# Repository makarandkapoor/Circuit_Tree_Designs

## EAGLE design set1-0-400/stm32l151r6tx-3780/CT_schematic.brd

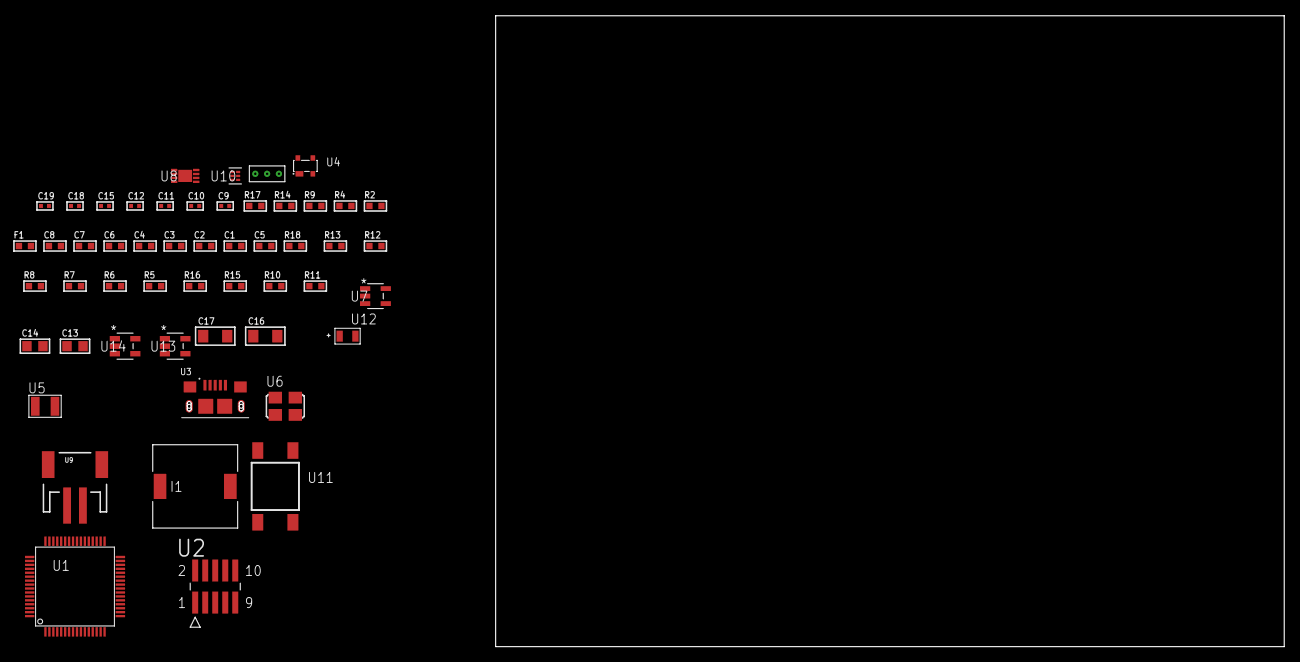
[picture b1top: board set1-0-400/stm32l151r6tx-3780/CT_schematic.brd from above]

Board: 2 copper layers, 52 parts (0 on the bottom side), 30 nets, no tracks yet.

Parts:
C1, C2, C3, C4, C6: 1e-07; C0603
C5: 4.7e-06; C0603
C7: 1e-08; C0603
C8: 1e-06; C0603
C9, C10: 1e-11; C0402
C11, C15: 1e-07; C0402
C12, C18, C19: 1e-08; C0402
C13, C14: 1e-05; C0805
C16, C17: 1e-05; C1206
F1: 240.0; L0603
I1: 3.8e-06; DR1040
R2: 1000.0; R0603
R4: 4700.0; R0603
R5, R6, R7, R8, R12, R13, R18: 10000.0; R0603
R9: 5.0; R0603
R10: 220000.0; R0603
R11: 1000000.0; R0603
R14: 9100.0; R0603
R15: 680000.0; R0603
R16: 120000.0; R0603
R17: 2000.0; R0603
U1: STM32L151R6T6; LQFP64
U2: FTSH-105-01-L-DV-K; SAMTEC_FTSH-105-01-L-DV-K
U3: 10118193-0001LF; FCI_10118193-0001LF
U4: prtr5v0u2ax; SOT143B
U5: ABS07-32.768KHZ-7-T
U6: ASFL1-25MHZ-NCS; ASFL1
U7: ltc3406es5; TSOT-23-5
U8: MCP73831T-2ACI/MC; DFN8_2X3MC
U9: S2B-PH-SM4-TB(LF)(SN); JST-2-SMD
U10: TPS3895ADRYR; SON-6
U11: 4-1437565-2; SW_4-1437565-2
U12: Q65110A2395; LGM67K-G1J2-24-Z
U13, U14: nc7sz125m5x; NC7SZ125M5X
U15: Dummy; DUMMY_PACKAGE_112

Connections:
CLK_CRYSTAL_U1_3: C9.1, U1.3, U5.1
CLK_CRYSTAL_U1_4: C10.1, U1.4, U5.2
CLK_U1_5: U1.5, U6.3
GND: C1.2, C2.2, C3.2, C4.2, C5.2, C6.2, C7.2, C8.2, C9.2, C10.2, C11.2, C12.2, C13.2, C14.1, C14.2, C15.2, C16.2, C17.2, C18.2, C19.2, R2.2, R5.2, R9.2, R10.2, R14.2, R16.2, R17.2, U1.12, U1.18, U1.31, U1.47, U1.63, U2.3, U2.5, U3.5, U3.6, U3.7, U3.8, U3.9, U4.1, U6.2, U7.2, U8.6, U8.9, U9.2, U10.2, U12.C, U13.2, U13.3, U14.1, U14.3, U15.1
INPUT_USBPOWER_5V: C16.1, R18.2, U3.1, U4.4, U8.1, U8.2
NET_U1_1: C6.1, U1.1
NET_U1_7: R4.1, U1.7, U14.4
NET_U1_13: C7.1, C8.1, F1.1, U1.13
NET_U1_60: R5.1, U1.60
NET_U1_62: U11.3, U11.4
NET_U2_9: R9.1, U2.9
NET_U7_3: I1.1, U7.3
NET_U7_5: R10.1, R11.1, U7.5
NET_U7_ATNET_3: I1.2, R11.2
NET_U8_5: R18.1, U8.5
NET_U8_8: R17.1, U8.8
NET_U10_1: R13.1, R14.1, U10.1
NET_U10_3: R15.2, R16.1, U10.3
NET_U10_4: R12.1, U10.4, U13.4, U14.2
NET_U11_1: R2.1, U11.1, U11.2
PROC_SYS_JTCK_SWCLK: R7.1, U1.49, U2.4
PROC_SYS_JTDO_TRACESWO: U1.55, U2.6
PROC_SYS_JTMS_SWDIO: R8.1, U1.46, U2.2
PROC_TIM10_CH1: U1.22, U15.2
PROC_TIM11_CH1: U1.23, U15.3
PROC_USB_DM: U1.44, U3.2, U4.3
PROC_USB_DP: U1.45, U3.3, U4.2
RST_OUT_U2_JTAG_RST_B: R6.1, U2.10, U13.1
VCC_S1_3V7: C13.1, C17.1, U7.4, U8.3, U8.4, U9.1
VCC_TIER1_3V3: C1.1, C2.1, C3.1, C4.1, C5.1, C11.1, C12.1, C14.2, C15.1, C18.1, C19.1, F1.2, I1.2, R4.2, R6.2, R7.2, R8.2, R11.2, R12.2, R13.2, R15.1, U1.19, U1.32, U1.48, U1.64, U2.1, U6.4, U10.6, U13.5, U14.5

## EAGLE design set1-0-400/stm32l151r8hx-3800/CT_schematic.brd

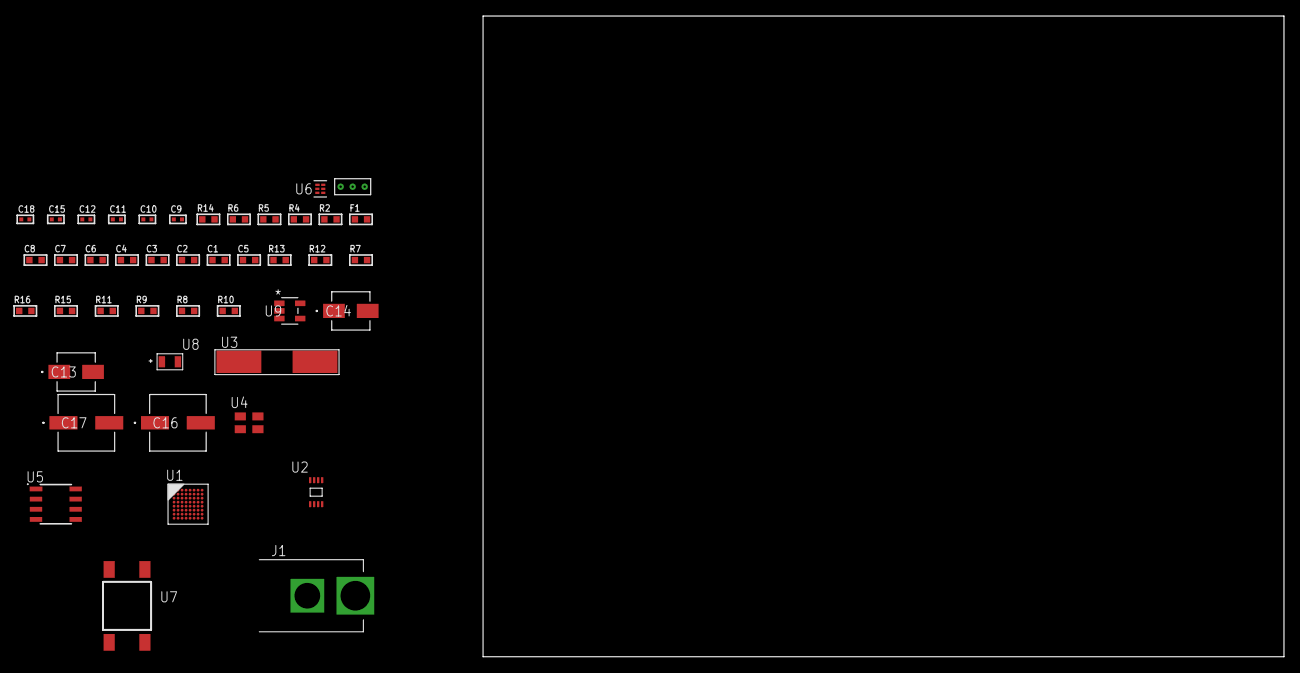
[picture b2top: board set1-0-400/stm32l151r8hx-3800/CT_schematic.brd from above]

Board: 2 copper layers, 100.0 x 80.0 mm, 44 parts (0 on the bottom side), 22 nets, no tracks yet.

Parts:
C1, C2, C3, C4, C6: 1e-07; C0603
C5: 4.7e-06; C0603
C7: 1e-08; C0603
C8: 1e-06; C0603
C9, C10: 1e-11; C0402
C11, C12, C18: 1e-08; C0402
C13: 1e-06; EXV-9B
C14: 2.2e-06; EXV-9B
C15: 1e-07; C0402
C16, C17: 0.0001; EXV-9H
F1: 240.0; L0603
J1: PJ-037B; PJ-037B_PACKAGE
R2: 1000.0; R0603
R4: 4700.0; R0603
R5, R6: 2200.0; R0603
R7, R12, R13: 10000.0; R0603
R8, R9, R11: 100000.0; R0603
R10: 164658.62; R0603
R14: 9100.0; R0603
R15: 680000.0; R0603
R16: 120000.0; R0603
U1: STM32L151R8H6; TFBGA64
U2: 24AA16-I/MC; TDFN-8/6MM
U3: ABLS-25.000MHZ-B2F-T
U4: ASEK-32.768KHz-ECST; ASEK
U5: LP2954AIMX/NOPB; LP2954
U6: TPS3895ADRYR; SON-6
U7: 4-1437565-2; SW_4-1437565-2
U8: Q65110A2395; LGM67K-G1J2-24-Z
U9: nc7sz125m5x; NC7SZ125M5X
U10: Dummy; DUMMY_PACKAGE_90

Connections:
CLK_CRYSTAL_U1_C1: C9.1, U1.C1, U3.1
CLK_CRYSTAL_U1_D1: C10.1, U1.D1, U3.2
CLK_U1_A1: U1.A1, U4.3
GND: C1.2, C2.2, C3.2, C4.2, C5.2, C6.2, C7.2, C8.2, C9.2, C10.2, C11.2, C12.2, C13.2, C14.2, C15.2, C16.2, C17.2, C18.2, J1.2, R2.2, R7.2, R11.2, R14.2, R16.2, U1.C2, U1.D4, U1.D5, U1.D6, U1.F1, U2.4, U2.7, U4.2, U5.4, U6.2, U8.C, U9.1, U9.3, U10.1
NET_U1_A3: R6.1, U1.A3, U2.5
NET_U1_B2: C6.1, U1.B2
NET_U1_B3: R5.1, U1.B3, U2.6
NET_U1_B4: R7.1, U1.B4
NET_U1_E1: R4.1, U1.E1, U9.4
NET_U1_H1: C7.1, C8.1, F1.1, U1.G1, U1.H1
NET_U1_H8: U7.3, U7.4
NET_U5_3: R9.1, U5.3
NET_U5_5: R8.1, U5.5
NET_U5_7: R10.2, R11.1, U5.7
NET_U6_1: R13.1, R14.1, U6.1
NET_U6_3: R15.2, R16.1, U6.3
NET_U6_4: R12.1, U6.4, U9.2
NET_U7_1: R2.1, U7.1, U7.2
PROC_TIM2_CH1: U1.A6, U10.3
PROC_TIM2_CH3: U1.F3, U10.2
VCC_S1_5V6: C13.1, C16.1, C17.1, J1.1, R9.2, U5.8
VCC_TIER1_3V3: C1.1, C2.1, C3.1, C4.1, C5.1, C11.1, C12.1, C14.1, C15.1, C18.1, F1.2, R4.2, R5.2, R6.2, R8.2, R10.1, R12.2, R13.2, R15.1, U1.D2, U1.E4, U1.E5, U1.E6, U2.8, U4.4, U5.1, U6.6, U9.5

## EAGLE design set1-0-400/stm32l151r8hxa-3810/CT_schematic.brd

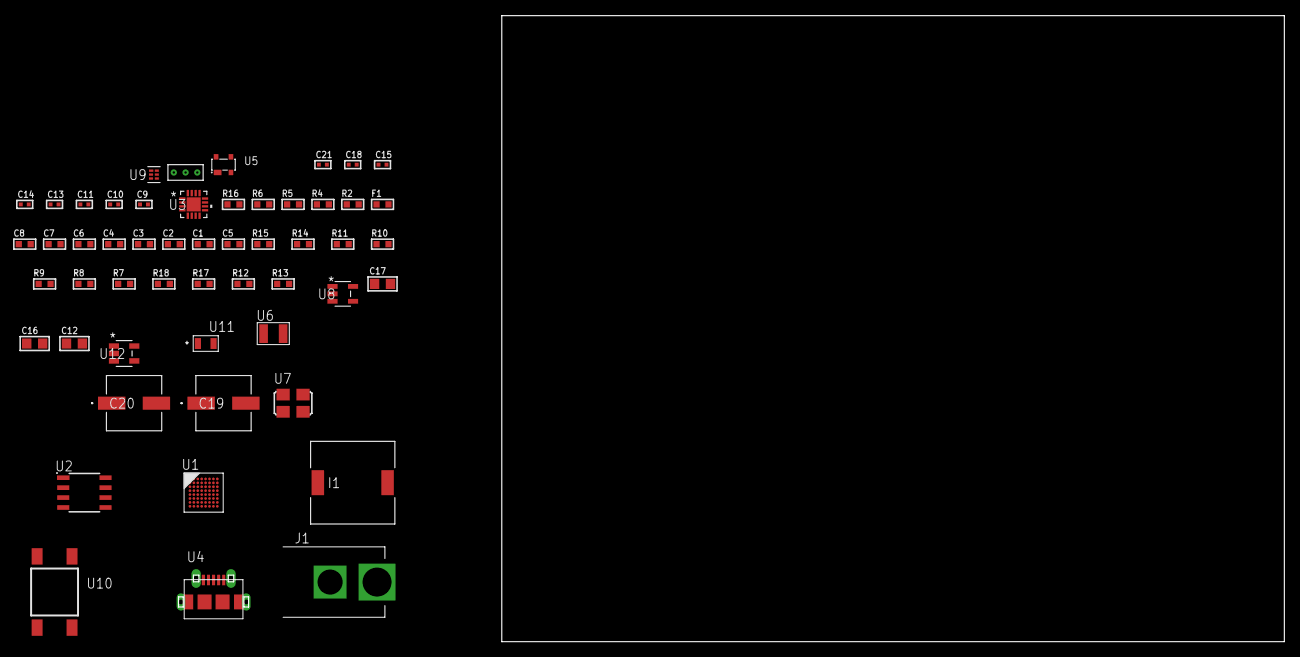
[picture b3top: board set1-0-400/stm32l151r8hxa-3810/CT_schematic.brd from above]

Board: 2 copper layers, 53 parts (0 on the bottom side), 33 nets, no tracks yet.

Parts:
C1, C2, C3, C4, C6: 1e-07; C0603
C5: 4.7e-06; C0603
C7: 1e-08; C0603
C8: 1e-06; C0603
C9, C10: 1e-11; C0402
C11, C15, C21: 1e-08; C0402
C12: 4.7e-06; C0805
C13, C14, C18: 1e-07; C0402
C16, C17: 1e-05; C0805
C19, C20: 0.0001; EXV-9H
F1: 240.0; L0603
I1: 8.2e-06; DR1040
J1: PJ-037B; PJ-037B_PACKAGE
R2: 1000.0; R0603
R4: 4700.0; R0603
R5, R6: 2200.0; R0603
R7, R8, R9, R10, R11, R14, R15: 10000.0; R0603
R12: 220000.0; R0603
R13: 1000000.0; R0603
R16: 9100.0; R0603
R17: 680000.0; R0603
R18: 120000.0; R0603
U1: STM32L151R8H6A; TFBGA64
U2: AT25M02-SSHD-T; SOIC-8
U3: MMA8451QT; QFN-16
U4: 47590-0001; MICRO_USB_AB
U5: prtr5v0u2ax; SOT143B
U6: ABS07-32.768KHZ-7-T
U7: ASFL1-25MHZ-NCS; ASFL1
U8: ltc3406es5; TSOT-23-5
U9: TPS3895ADRYR; SON-6
U10: 4-1437565-2; SW_4-1437565-2
U11: Q65110A2395; LGM67K-G1J2-24-Z
U12: nc7sz125m5x; NC7SZ125M5X
U13: Dummy; DUMMY_PACKAGE_111

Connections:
CLK_CRYSTAL_U1_A1: C9.1, U1.A1, U6.1
CLK_CRYSTAL_U1_B1: C10.1, U1.B1, U6.2
CLK_U1_C1: U1.C1, U7.3
GND: C1.2, C2.2, C3.2, C4.2, C5.2, C6.2, C7.2, C8.2, C9.2, C10.2, C11.2, C12.2, C13.2, C14.2, C15.2, C16.2, C17.1, C17.2, C18.2, C19.2, C20.2, C21.2, J1.2, R2.2, R7.2, R11.2, R12.2, R16.2, R18.2, U1.C2, U1.D4, U1.D5, U1.D6, U1.F1, U2.4, U3.5, U3.10, U3.12, U3.17, U4.5, U4.6, U4.7, U4.8, U4.9, U5.1, U7.2, U8.2, U9.2, U11.C, U12.1, U12.3, U13.1
NET_U1_A3: R6.1, U1.A3, U3.6
NET_U1_B2: C6.1, U1.B2
NET_U1_B3: R5.1, U1.B3, U3.4
NET_U1_B4: R7.1, U1.B4
NET_U1_E1: R4.1, U1.E1, U12.4
NET_U1_H1: C7.1, C8.1, F1.1, U1.G1, U1.H1
NET_U1_H8: U10.3, U10.4
NET_U2_3: R8.1, U2.3
NET_U2_7: R10.1, U2.7
NET_U3_2: C14.1, U3.2
NET_U3_7: R11.1, U3.7
NET_U5_4: U4.1, U5.4
NET_U8_3: I1.1, U8.3
NET_U8_5: R12.1, R13.1, U8.5
NET_U8_ATNET_3: I1.2, R13.2
NET_U9_1: R15.1, R16.1, U9.1
NET_U9_3: R17.2, R18.1, U9.3
NET_U9_4: R14.1, U9.4, U12.2
NET_U10_1: R2.1, U10.1, U10.2
PROC_SPI1_MISO: U1.A4, U2.2
PROC_SPI1_MOSI: U1.C4, U2.5
PROC_SPI1_NSS: R9.1, U1.A6, U2.1
PROC_SPI1_SCK: U1.A5, U2.6
PROC_TIM2_CH3: U1.F3, U13.2
PROC_TIM2_CH4: U1.G3, U13.3
PROC_USB_DM: U1.C8, U4.2, U5.3
PROC_USB_DP: U1.B8, U4.3, U5.2
VCC_S1_4V8: C16.1, C19.1, C20.1, J1.1, U8.4
VCC_TIER1_3V3: C1.1, C2.1, C3.1, C4.1, C5.1, C11.1, C12.1, C13.1, C15.1, C17.2, C18.1, C21.1, F1.2, I1.2, R4.2, R5.2, R6.2, R8.2, R9.2, R10.2, R13.2, R14.2, R15.2, R17.1, U1.D2, U1.E4, U1.E5, U1.E6, U2.8, U3.1, U3.14, U7.4, U9.6, U12.5

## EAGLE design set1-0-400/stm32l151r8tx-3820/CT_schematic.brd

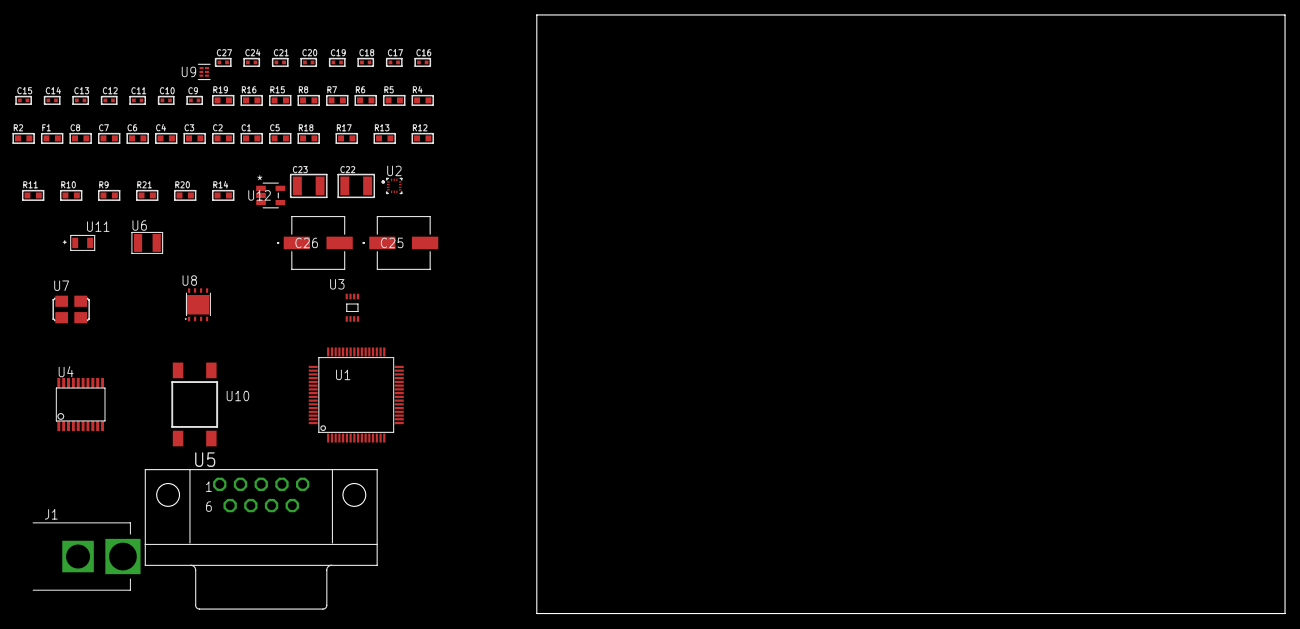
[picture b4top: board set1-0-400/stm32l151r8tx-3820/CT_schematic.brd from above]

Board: 2 copper layers, 100.0 x 80.0 mm, 60 parts (0 on the bottom side), 39 nets, no tracks yet.

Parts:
C1, C2, C3, C4, C6: 1e-07; C0603
C5: 4.7e-06; C0603
C7: 1e-08; C0603
C8: 1e-06; C0603
C9, C10: 1e-11; C0402
C11, C12, C14, C15, C16, C17, C18, C19, C24: 1e-07; C0402
C13, C20, C21, C27: 1e-08; C0402
C22, C23: 1e-05; C1210
C25, C26: 0.0001; EXV-9H
F1: 240.0; L0603
J1: PJ-037B; PJ-037B_PACKAGE
R2, R16: 1000.0; R0603
R4: 4700.0; R0603
R5, R6, R7, R8: 2200.0; R0603
R9, R10, R11, R12, R13, R17, R18: 10000.0; R0603
R14: 100000.0; R0603
R15: 2231.0; R0603
R19: 9100.0; R0603
R20: 680000.0; R0603
R21: 120000.0; R0603
U1: STM32L151R8T6; LQFP64
U2: BMC150; LGA14R35P5X6_200X200X100
U3: 24AA32AT-I/MNY; TDFN-8/6MM
U4: SP3203ECY-L/TR; TSSOP20-I
U5: 182-009-113R531; 182-009-MALE
U6: ABS07-32.768KHZ-7-T
U7: ASFL1-25MHZ-NCS; ASFL1
U8: LP3878SDX-ADJ/NOPB; WSON-8
U9: TPS3895ADRYR; SON-6
U10: 4-1437565-2; SW_4-1437565-2
U11: Q65110A2395; LGM67K-G1J2-24-Z
U12: nc7sz125m5x; NC7SZ125M5X

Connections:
CLK_CRYSTAL_U1_3: C9.1, U1.3, U6.1
CLK_CRYSTAL_U1_4: C10.1, U1.4, U6.2
CLK_U1_5: U1.5, U7.3
GND: C1.2, C2.2, C3.2, C4.2, C5.2, C6.2, C7.2, C8.2, C9.2, C10.2, C11.2, C12.2, C13.2, C14.2, C15.2, C18.2, C19.2, C20.2, C21.2, C22.2, C23.2, C24.2, C25.2, C26.2, C27.2, J1.2, R2.2, R9.2, R11.2, R12.2, R16.2, R19.2, R21.2, U1.12, U1.18, U1.31, U1.47, U1.63, U2.1, U2.6, U2.7, U2.9, U3.4, U4.18, U5.5, U7.2, U8.3, U8.PAD, U9.2, U11.C, U12.1, U12.3
NET_U1_1: C6.1, U1.1
NET_U1_7: R4.1, U1.7, U12.4
NET_U1_13: C7.1, C8.1, F1.1, U1.13
NET_U1_29: R7.1, U1.29, U3.6
NET_U1_30: R8.1, U1.30, U3.5
NET_U1_58: R5.1, U1.58, U2.11
NET_U1_59: R6.1, U1.59, U2.14
NET_U1_60: R9.1, U1.60
NET_U1_62: U10.3, U10.4
NET_U3_1: R11.1, U3.1
NET_U3_2: R12.1, U3.2
NET_U3_3: R13.1, U3.3
NET_U4_1: C16.1, U4.1
NET_U4_2: C18.1, U4.2
NET_U4_3: C16.2, U4.3
NET_U4_4: C17.1, U4.4
NET_U4_5: C17.2, U4.5
NET_U4_6: C19.1, U4.6
NET_U5_2: U4.14, U5.2
NET_U5_3: U4.17, U5.3
NET_U5_7: U4.13, U5.7
NET_U5_8: U4.16, U5.8
NET_U8_1: C21.1, U8.1
NET_U8_6: R15.2, R16.1, U8.6
NET_U8_8: R14.1, U8.8
NET_U9_1: R18.1, R19.1, U9.1
NET_U9_3: R20.2, R21.1, U9.3
NET_U9_4: R17.1, U9.4, U12.2
NET_U10_1: R2.1, U10.1, U10.2
PROC_USART1_CTS: U1.44, U4.8
PROC_USART1_RTS: U1.45, U4.10
PROC_USART1_RX: U1.43, U4.11
PROC_USART1_TX: U1.42, U4.7
VCC_S1_12V7: C22.1, C25.1, C26.1, J1.1, R14.2, U8.4
VCC_TIER1_3V3: C1.1, C2.1, C3.1, C4.1, C5.1, C11.1, C12.1, C13.1, C14.1, C15.1, C20.1, C23.1, C24.1, C27.1, F1.2, R4.2, R5.2, R6.2, R7.2, R8.2, R10.1, R10.2, R13.2, R15.1, R17.2, R18.2, R20.1, U1.19, U1.32, U1.48, U1.64, U2.8, U2.10, U2.12, U2.13, U3.7, U3.8, U4.12, U4.19, U7.4, U8.5, U9.6, U12.5

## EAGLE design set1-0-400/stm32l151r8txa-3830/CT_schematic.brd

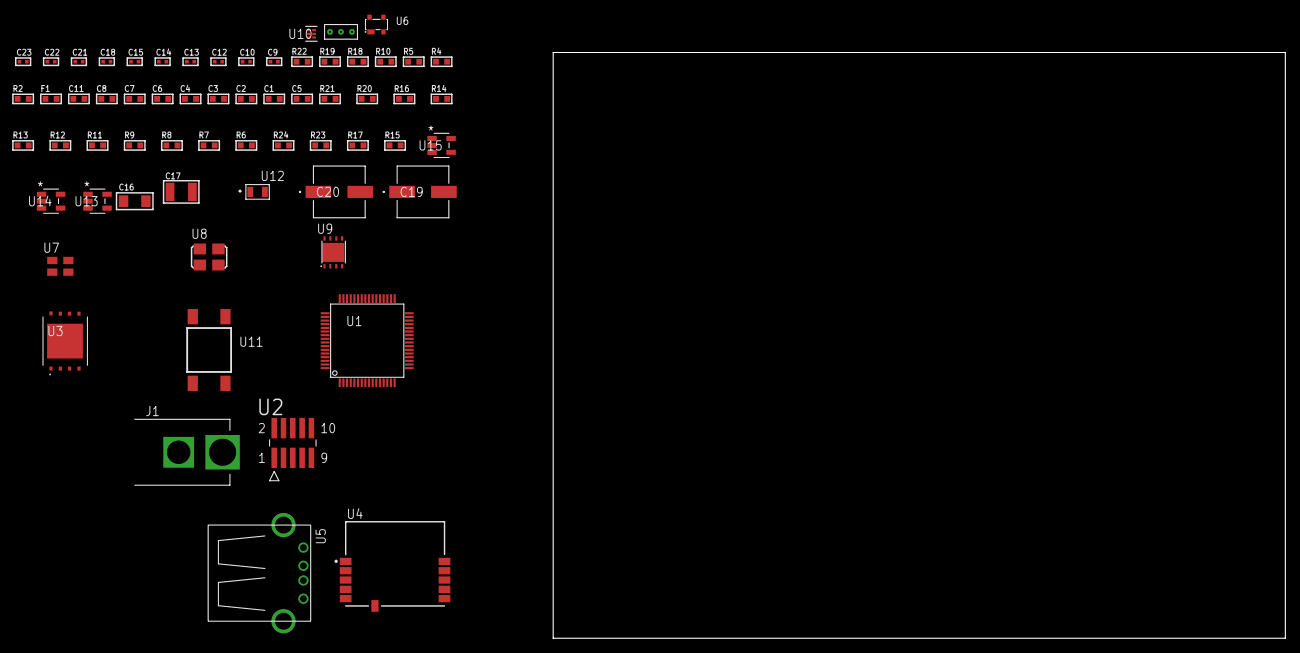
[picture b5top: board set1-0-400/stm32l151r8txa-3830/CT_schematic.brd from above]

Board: 2 copper layers, 100.0 x 80.0 mm, 63 parts (0 on the bottom side), 39 nets, no tracks yet.

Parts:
C1, C2, C3, C4, C6: 1e-07; C0603
C5: 4.7e-06; C0603
C7: 1e-08; C0603
C8, C11: 1e-06; C0603
C9, C12, C18: 1e-07; C0402
C10, C13, C14, C15, C21, C22, C23: 1e-08; C0402
C16: 1e-05; C1206
C17: 1e-05; C1210
C19, C20: 0.0001; EXV-9H
F1: 240.0; L0603
J1: PJ-037B; PJ-037B_PACKAGE
R2, R19: 1000.0; R0603
R4, R5: 4700.0; R0603
R6, R7, R8, R9, R11, R12, R13, R14, R20, R21: 10000.0; R0603
R10: 5.0; R0603
R15, R17: 100000.0; R0603
R16: 47000.0; R0603
R18: 2231.0; R0603
R22: 9100.0; R0603
R23: 680000.0; R0603
R24: 120000.0; R0603
U1: STM32L151R8T6A; LQFP64
U2: FTSH-105-01-L-DV-K; SAMTEC_FTSH-105-01-L-DV-K
U3: S25FL128SDPNFI001; WNG008
U4: SPBTLE-RF; XCVR_SPBTLE-RF
U5: 61400416021; USB-A-H
U6: prtr5v0u2ax; SOT143B
U7: ASEK-32.768KHz-ECST; ASEK
U8: ASFL1-25MHZ-NCS; ASFL1
U9: LP3878SDX-ADJ/NOPB; WSON-8
U10: TPS3895ADRYR; SON-6
U11: 4-1437565-2; SW_4-1437565-2
U12: Q65110A2395; LGM67K-G1J2-24-Z
U13, U14, U15: nc7sz125m5x; NC7SZ125M5X
U16: Dummy; DUMMY_PACKAGE_140

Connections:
CLK_U1_3: U1.3, U7.3
CLK_U1_5: U1.5, U8.3
GND: C1.2, C2.2, C3.2, C4.2, C5.2, C6.2, C7.2, C8.2, C9.2, C10.2, C11.2, C12.2, C13.2, C14.2, C15.2, C16.2, C17.2, C18.2, C19.2, C20.2, C21.2, C22.2, C23.2, J1.2, R2.2, R6.2, R10.2, R15.2, R16.2, R19.2, R22.2, R24.2, U1.12, U1.18, U1.31, U1.47, U1.63, U2.3, U2.5, U3.4, U3.PAD, U4.6, U5.4, U5.5, U5.6, U6.1, U7.2, U8.2, U9.3, U9.PAD, U10.2, U12.C, U13.2, U13.3, U14.1, U14.3, U15.1, U15.3, U16.1
NET_U1_1: C6.1, U1.1
NET_U1_7: R5.1, U1.7, U15.4
NET_U1_13: C7.1, C8.1, F1.1, U1.13
NET_U1_60: R6.1, U1.60
NET_U1_62: U11.3, U11.4
NET_U2_9: R10.1, U2.9
NET_U3_3: R11.1, U3.3
NET_U3_7: R13.1, U3.7
NET_U4_11: R4.1, U4.11, U14.4
NET_U6_4: U5.1, U6.4
NET_U9_1: C15.1, U9.1
NET_U9_6: R18.2, R19.1, U9.6
NET_U9_8: R17.1, U9.8
NET_U10_1: R21.1, R22.1, U10.1
NET_U10_3: R23.2, R24.1, U10.3
NET_U10_4: R20.1, U10.4, U13.4, U14.2, U15.2
NET_U11_1: R2.1, U11.1, U11.2
PROC_GPIO_TO_U4_SPI_IRQ: R16.1, U1.2, U4.4
PROC_PC15_OSC32_OUT: U1.4, U16.2
PROC_PH1_OSC_OUT: U1.6, U16.3
PROC_SPI1_MISO: U1.22, U4.8
PROC_SPI1_MOSI: U1.23, U4.9
PROC_SPI1_NSS: R14.1, U1.20, U4.10
PROC_SPI1_SCK: R15.1, U1.21, U4.7
PROC_SPI2_MISO: U1.35, U3.2
PROC_SPI2_MOSI: U1.36, U3.5
PROC_SPI2_NSS: R12.1, U1.33, U3.1
PROC_SPI2_SCK: U1.34, U3.6
PROC_SYS_JTCK_SWCLK: R8.1, U1.49, U2.4
PROC_SYS_JTDO_TRACESWO: U1.55, U2.6
PROC_SYS_JTMS_SWDIO: R9.1, U1.46, U2.2
PROC_USB_DM: U1.44, U5.2, U6.3
PROC_USB_DP: U1.45, U5.3, U6.2
RST_OUT_U2_JTAG_RST_B: R7.1, U2.10, U13.1
VCC_S1_9V4: C16.1, C19.1, C20.1, J1.1, R17.2, U9.4
VCC_TIER1_3V3: C1.1, C2.1, C3.1, C4.1, C5.1, C9.1, C10.1, C11.1, C12.1, C13.1, C14.1, C17.1, C18.1, C21.1, C22.1, C23.1, F1.2, R4.2, R5.2, R7.2, R8.2, R9.2, R11.2, R12.2, R13.2, R14.2, R18.1, R20.2, R21.2, R23.1, U1.19, U1.32, U1.48, U1.64, U2.1, U3.8, U4.5, U7.4, U8.4, U9.5, U10.6, U13.5, U14.5, U15.5

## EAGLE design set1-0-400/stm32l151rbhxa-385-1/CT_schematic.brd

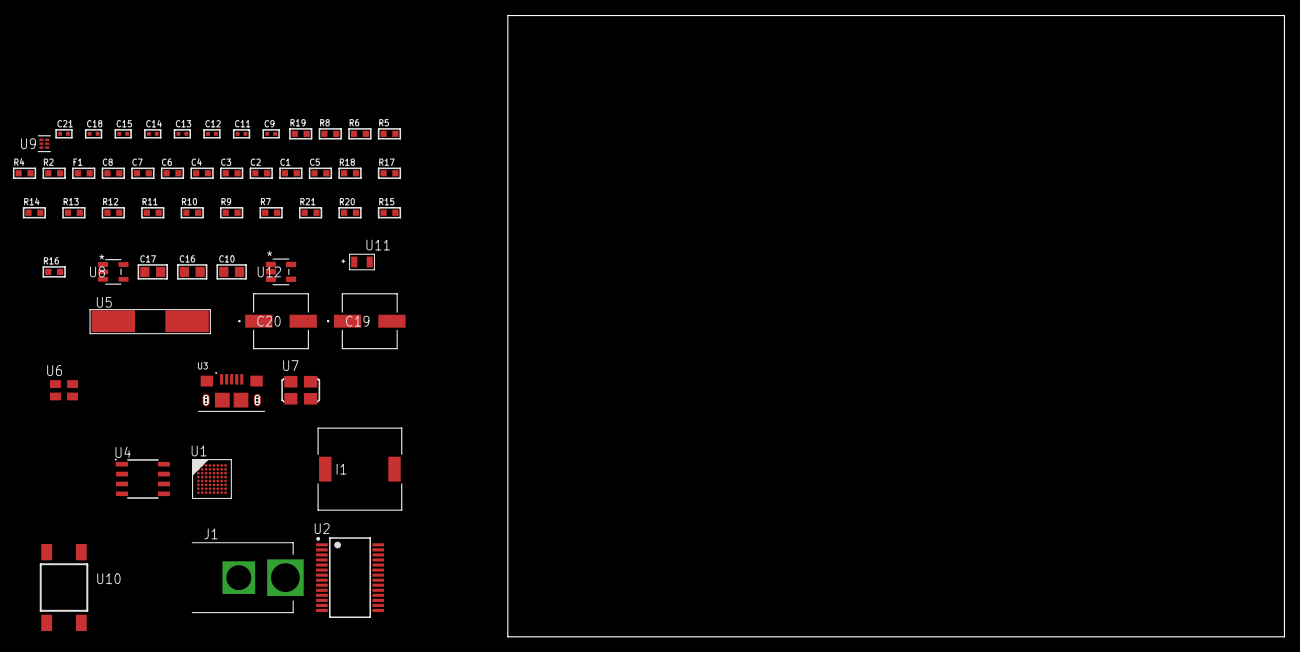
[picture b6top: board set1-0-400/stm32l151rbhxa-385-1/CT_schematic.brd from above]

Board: 2 copper layers, 55 parts (0 on the bottom side), 35 nets, no tracks yet.

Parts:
C1, C2, C3, C4, C6: 1e-07; C0603
C5: 4.7e-06; C0603
C7: 1e-08; C0603
C8: 1e-06; C0603
C9, C11, C12, C13, C18: 1e-07; C0402
C10: 4.7e-06; C0805
C14, C15, C21: 1e-08; C0402
C16, C17: 1e-05; C0805
C19, C20: 0.0001; EXV-9H
F1: 240.0; L0603
I1: 5.2e-06; DR1040
J1: PJ-037B; PJ-037B_PACKAGE
R2: 1000.0; R0603
R4, R8: 4700.0; R0603
R5, R6: 2200.0; R0603
R7, R9, R10, R11, R12, R13, R14, R17, R18: 10000.0; R0603
R15: 220000.0; R0603
R16: 1000000.0; R0603
R19: 9100.0; R0603
R20: 680000.0; R0603
R21: 120000.0; R0603
U1: STM32L151RBH6A; TFBGA64
U2: FT232RL-REEL; SSOP-28
U3: 10118193-0001LF; FCI_10118193-0001LF
U4: TMP75BID; SOIC-8
U5: ABLS-12.000MHZ-B4-T
U6: ASEK-32.768KHz-ECST; ASEK
U7: ASFL1-25MHZ-NCS; ASFL1
U8: ltc3406es5; TSOT-23-5
U9: TPS3895ADRYR; SON-6
U10: 4-1437565-2; SW_4-1437565-2
U11: Q65110A2395; LGM67K-G1J2-24-Z
U12: nc7sz125m5x; NC7SZ125M5X

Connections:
CLK_CRYSTAL_U2_27: U2.27, U5.1
CLK_CRYSTAL_U2_28: U2.28, U5.2
CLK_U1_A1: U1.A1, U6.3
CLK_U1_C1: U1.C1, U7.3
GND: C1.2, C2.2, C3.2, C4.2, C5.2, C6.2, C7.2, C8.2, C9.2, C10.2, C11.2, C12.2, C13.2, C14.2, C15.2, C16.2, C17.1, C17.2, C18.2, C19.2, C20.2, C21.2, J1.2, R2.2, R7.2, R10.2, R13.2, R15.2, R19.2, R21.2, U1.C2, U1.D4, U1.D5, U1.D6, U1.F1, U2.7, U2.18, U2.21, U2.25, U2.26, U3.5, U3.6, U3.7, U3.8, U3.9, U4.4, U6.2, U7.2, U8.2, U9.2, U11.C, U12.1, U12.3
NET_U1_A3: R6.1, U1.A3, U4.1
NET_U1_B2: C6.1, U1.B2
NET_U1_B3: R5.1, U1.B3, U4.2
NET_U1_B4: R7.1, U1.B4
NET_U1_E1: R4.1, U1.E1, U12.4
NET_U1_H1: C7.1, C8.1, F1.1, U1.G1, U1.H1
NET_U1_H8: U10.3, U10.4
NET_U2_14: R9.1, U2.14
NET_U2_17: C11.1, U2.17
NET_U2_19: R10.1, U2.19
NET_U3_1: R8.1, U3.1
NET_U3_2: U2.16, U3.2
NET_U3_3: U2.15, U3.3
NET_U4_3: R11.1, U4.3
NET_U4_5: R14.1, U4.5
NET_U4_6: R13.1, U4.6
NET_U4_7: R12.1, U4.7
NET_U8_3: I1.1, U8.3
NET_U8_5: R15.1, R16.1, U8.5
NET_U8_ATNET_3: I1.2, R16.2
NET_U9_1: R18.1, R19.1, U9.1
NET_U9_3: R20.2, R21.1, U9.3
NET_U9_4: R17.1, U9.4, U12.2
NET_U10_1: R2.1, U10.1, U10.2
PROC_USART1_CTS: U1.C8, U2.3
PROC_USART1_RTS: U1.B8, U2.11
PROC_USART1_RX: U1.C3, U2.1
PROC_USART1_TX: U1.C7, U2.5
VCC_S1_5V2: C16.1, C19.1, C20.1, J1.1, U8.4
VCC_TIER1_3V3: C1.1, C2.1, C3.1, C4.1, C5.1, C9.1, C10.1, C12.1, C13.1, C14.1, C15.1, C17.2, C18.1, C21.1, F1.2, I1.2, R4.2, R5.2, R6.2, R9.2, R11.2, R12.2, R14.2, R16.2, R17.2, R18.2, R20.1, U1.D2, U1.E4, U1.E5, U1.E6, U2.4, U2.20, U4.8, U6.4, U7.4, U9.6, U12.5

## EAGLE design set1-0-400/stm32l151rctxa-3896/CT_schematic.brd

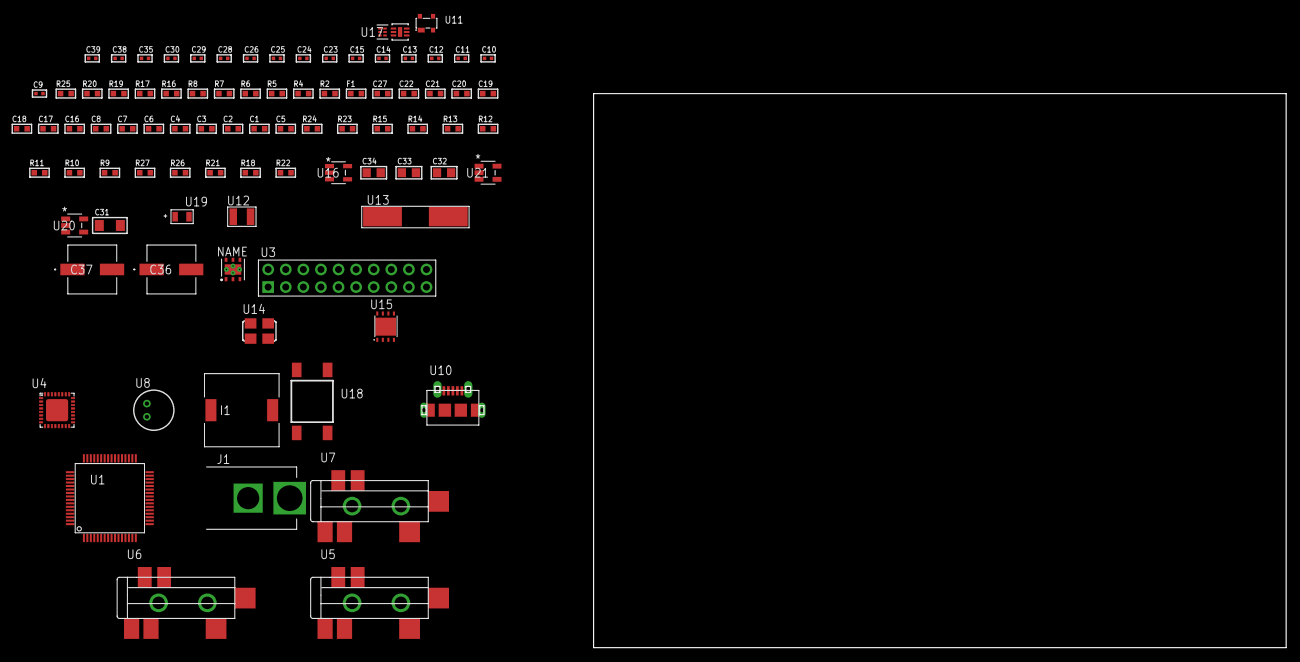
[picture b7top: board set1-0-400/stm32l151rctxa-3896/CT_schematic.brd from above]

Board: 2 copper layers, 124.8 x 80.0 mm, 88 parts (0 on the bottom side), 54 nets, no tracks yet.

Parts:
C1, C2, C3, C4, C6: 1e-07; C0603
C5: 4.7e-06; C0603
C7: 1e-08; C0603
C8, C16, C17, C18, C19, C20, C21, C22, C27: 1e-06; C0603
C9, C10, C11, C12: 1e-11; C0402
C13, C29, C30, C38, C39: 1e-08; C0402
C14, C15, C23, C24, C25, C26, C28, C35: 1e-07; C0402
C31: 1e-05; C1206
C32, C33, C34: 1e-05; C0805
C36, C37: 0.0001; EXV-9H
F1: 240.0; L0603
I1: 5.2e-06; DR1040
J1: PJ-037B; PJ-037B_PACKAGE
R2, R20: 1000.0; R0603
R4: 4700.0; R0603
R5, R6, R7, R8: 2200.0; R0603
R9, R10, R11, R12, R13, R14, R15, R23, R24: 10000.0; R0603
R16, R17: 1270.0; R0603
R18: 100000.0; R0603
R19: 200.0; R0603
R21: 220000.0; R0603
R22: 1000000.0; R0603
R25: 9100.0; R0603
R26: 680000.0; R0603
R27: 120000.0; R0603
U1: STM32L151RCT6A; LQFP64
U2: HDC1080DMBR; WSON-6
U3: TST-110-05-T-D-RA
U4: SGTL5000XNAA3; QFN-32
U5, U6, U7: SJ-43515TS-SMT-TR
U8: WM-64PCT; WM-64PC
U9: SI7006-A20-IM; DFN-6
U10: 47590-0001; MICRO_USB_AB
U11: prtr5v0u2ax; SOT143B
U12: ABS07-32.768KHZ-7-T
U13: ABLS-25.000MHZ-B2F-T
U14: ASFL-24.57MHZ-NCS; ASFL1
U15: LP3878SDX-ADJ/NOPB; WSON-8
U16: ltc3406es5; TSOT-23-5
U17: TPS3895ADRYR; SON-6
U18: 4-1437565-2; SW_4-1437565-2
U19: Q65110A2395; LGM67K-G1J2-24-Z
U20, U21: nc7sz125m5x; NC7SZ125M5X

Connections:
CLK_CRYSTAL_U1_3: C9.1, U1.3, U12.1
CLK_CRYSTAL_U1_4: C10.1, U1.4, U12.2
CLK_CRYSTAL_U1_5: C11.1, U1.5, U13.1
CLK_CRYSTAL_U1_6: C12.1, U1.6, U13.2
CLK_U4_21: U4.21, U14.3
GND: C1.2, C2.2, C3.2, C4.2, C5.2, C6.2, C7.2, C8.2, C9.2, C10.2, C11.2, C12.2, C13.2, C14.2, C15.2, C23.2, C24.2, C25.2, C26.2, C27.2, C28.2, C29.2, C30.2, C31.2, C32.2, C33.2, C34.1, C34.2, C35.2, C36.2, C37.2, C38.2, C39.2, J1.2, R2.2, R9.2, R15.2, R17.2, R20.2, R21.2, R25.2, R27.2, U1.12, U1.18, U1.31, U1.47, U1.63, U2.2, U2.PAD, U3.4, U3.6, U3.8, U3.10, U3.12, U3.14, U3.16, U3.18, U3.20, U4.1, U4.3, U4.7, U4.EXP, U6.1, U7.1, U8.2, U9.2, U9.7, U10.5, U10.6, U10.7, U10.8, U10.9, U11.1, U14.2, U15.3, U15.PAD, U16.2, U17.2, U19.C, U20.2, U20.3, U21.1, U21.3
NET_U1_1: C6.1, U1.1
NET_U1_7: R4.1, U1.7, U21.4
NET_U1_13: C7.1, C8.1, F1.1, U1.13
NET_U1_29: R7.1, U1.29, U9.6
NET_U1_30: R8.1, U1.30, U9.1
NET_U1_58: R5.1, U1.58, U2.6
NET_U1_59: R6.1, U1.59, U2.1
NET_U1_60: R9.1, U1.60
NET_U1_62: U18.3, U18.4
NET_U3_19: R15.1, U3.19
NET_U4_10: C26.1, U4.10
NET_U4_29: R16.1, U4.29
NET_U4_31: R17.1, U4.31
NET_U5_1: U4.4, U5.1
NET_U5_2: U4.2, U5.2
NET_U5_5: U4.6, U5.5
NET_U6_2: C17.1, U6.2
NET_U6_5: C16.1, U6.5
NET_U7_2: C19.1, C20.1, U7.2
NET_U7_5: C18.1, U7.5
NET_U7_13: C19.2, C20.2
NET_U8_1: C21.1, C22.1, C27.1, U4.16, U8.1
NET_U8_15: C21.2, C22.2
NET_U11_4: U10.1, U11.4
NET_U15_1: C30.1, U15.1
NET_U15_6: R19.2, R20.1, U15.6
NET_U15_8: R18.1, U15.8
NET_U16_3: I1.1, U16.3
NET_U16_5: R21.1, R22.1, U16.5
NET_U16_ATNET_3: I1.2, R22.2
NET_U17_1: R24.1, R25.1, U17.1
NET_U17_3: R26.2, R27.1, U17.3
NET_U17_4: R23.1, U17.4, U20.4, U21.2
NET_U18_1: R2.1, U18.1, U18.2
PROC_I2S2_CK: U1.34, U4.24
PROC_I2S2_SD: U1.36, U4.26
PROC_I2S2_WS: U1.33, U4.23
PROC_SYS_JTCK_SWCLK: R13.1, U1.49, U3.9
PROC_SYS_JTDI: R11.1, U1.50, U3.5
PROC_SYS_JTDO_TRACESWO: U1.55, U3.13
PROC_SYS_JTMS_SWDIO: R12.1, U1.46, U3.7
PROC_SYS_JTRST: R10.1, U1.56, U3.3
PROC_USB_DM: U1.44, U10.2, U11.3
PROC_USB_DP: U1.45, U10.3, U11.2
RST_OUT_U3_SRESET_B: R14.1, U3.15, U20.1
VCC_S1_5V2: C31.1, C33.1, C36.1, C37.1, J1.1, R18.2, U15.4, U16.4
VCC_TIER1_1V2: C23.1, C32.1, R19.1, U4.30, U15.5
VCC_TIER1_3V3: C1.1, C2.1, C3.1, C4.1, C5.1, C13.1, C14.1, C15.1, C24.1, C25.1, C28.1, C29.1, C34.2, C35.1, C38.1, C39.1, F1.2, I1.2, R4.2, R5.2, R6.2, R7.2, R8.2, R10.2, R11.2, R12.2, R13.2, R14.2, R16.2, R22.2, R23.2, R24.2, R26.1, U1.19, U1.32, U1.48, U1.64, U2.5, U3.1, U3.2, U4.5, U4.20, U9.5, U14.4, U17.6, U20.5, U21.5
